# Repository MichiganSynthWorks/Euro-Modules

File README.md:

# Euro-Modules
Euro Module Projects

*[2HP2CV] 2HP Eurorack adaptapation of CVpal, orginal design be Emille Gillet / Mutable Instruments

License
=======

Code (AVR projects): GPL3.0.

Code (STM32F projects): MIT license.

Hardware: cc-by-sa-3.0

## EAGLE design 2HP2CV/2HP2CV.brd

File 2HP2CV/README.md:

# 2HP2CV USB to CV adapter

Based on [MI CV Pal](https://github.com/pichenettes/cvpal) by émilie gillet

License
=======

Code (AVR projects): GPL3.0.

Code (STM32F projects): MIT license.

Hardware: cc-by-sa-3.0

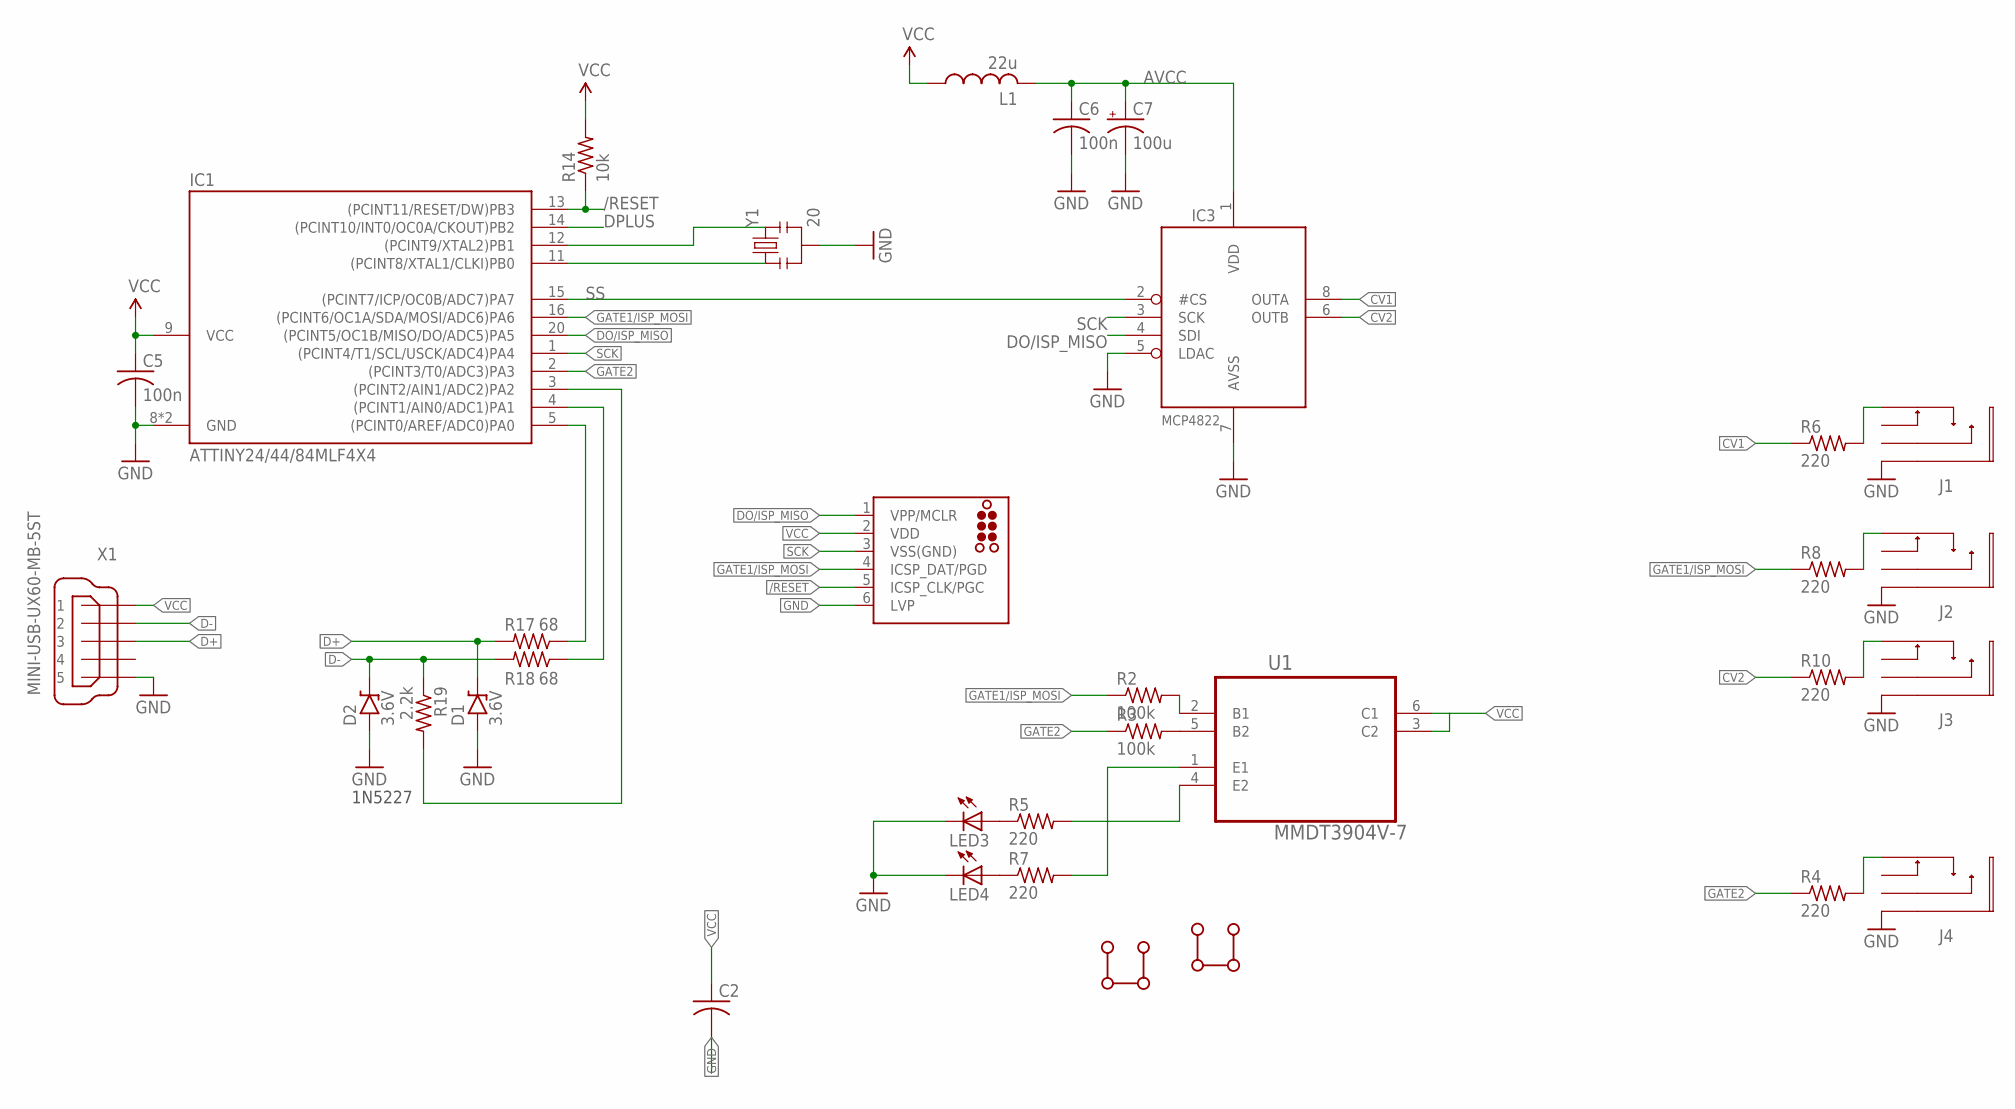
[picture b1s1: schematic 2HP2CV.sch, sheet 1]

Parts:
C2: C-USC0805K; C0805K
C5, C6: 100n; C0402
C7: 100u; A/3216-18R
D1, D2: 3.6V; SOD323-R
IC1: ATTINY24/44/84MLF4X4; MLF20-4X4
IC3: MCP4822SO08; SO08
J1, J2, J3, J4: PJ327E; PJ327
J5: TC2030-MCP-NL
L1: 22u; L2012C
LED3, LED4: LED3MM
R2, R3: 100k; R0402
R4, R5, R6, R7, R8, R10: 220; R0402
R14: 10k; R0402
R17, R18: 68; R0402
R19: 2.2k; R0402
U1: MMDT3904V-7; SOT50P170X60-6N
U$5, U$6: PCB-69M3
X1: MINI-USB-UX60-MB-5ST; UX60-MB-5ST
Y1: 20; RESONATOR-SMD

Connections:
/RESET: IC1.13 ((PCINT11/RESET/DW)PB3), J5.5 (ICSP_CLK/PGC), R14.1
AVCC: C6.1, C7.+, IC3.1 (VDD), L1.2
CV1: IC3.8 (OUTA), R6.1
CV2: IC3.6 (OUTB), R10.1
D+: D1.C, R17.2, X1.3
D-: D2.C, R18.2, R19.1, X1.2
DMINUS: IC1.4 ((PCINT1/AIN0/ADC1)PA1), R18.1
DO/ISP_MISO: IC1.20 ((PCINT5/OC1B/MISO/DO/ADC5)PA5), IC3.4 (SDI), J5.1 (VPP/MCLR)
DPLUS: IC1.5 ((PCINT0/AREF/ADC0)PA0), IC1.14 ((PCINT10/INT0/OC0A/CKOUT)PB2), R17.1
GATE1/ISP_MOSI: IC1.16 ((PCINT6/OC1A/SDA/MOSI/ADC6)PA6), J5.4 (ICSP_DAT/PGD), R2.1, R8.1
GATE2: IC1.2 ((PCINT3/T0/ADC3)PA3), R3.1, R4.1
GND: C2.2, C5.2, C6.2, C7.-, D1.A, D2.A, IC1.8 (GND), IC1.TH (GND), IC3.5 (LDAC), IC3.7 (AVSS), J1.P$1, J2.P$1, J3.P$1, J4.P$1, J5.6 (LVP), LED3.K (C), LED4.K (C), X1.5, Y1.2
unnamed: R3.2, U1.5 (B2)
unnamed: R2.2, U1.2 (B1)
unnamed: J4.P$2, R4.2
unnamed: J3.P$2, R10.2
unnamed: R5.2, U1.4 (E2)
unnamed: R7.2, U1.1 (E1)
unnamed: LED3.A, R5.1
unnamed: J1.P$2, R6.2
unnamed: LED4.A, R7.1
unnamed: J2.P$2, R8.2
unnamed: IC1.12 ((PCINT9/XTAL2)PB1), Y1.3
unnamed: IC1.11 ((PCINT8/XTAL1/CLKI)PB0), Y1.1
unnamed: IC1.3 ((PCINT2/AIN1/ADC2)PA2), R19.2
SCK: IC1.1 ((PCINT4/T1/SCL/USCK/ADC4)PA4), IC3.3 (SCK), J5.3 (VSS(GND))
SS: IC1.15 ((PCINT7/ICP/OC0B/ADC7)PA7), IC3.2 (#CS)
VCC: C2.1, C5.1, IC1.9 (VCC), J5.2 (VDD), L1.1, R14.2, U1.3 (C2), U1.6 (C1), X1.1

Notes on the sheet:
1N5227

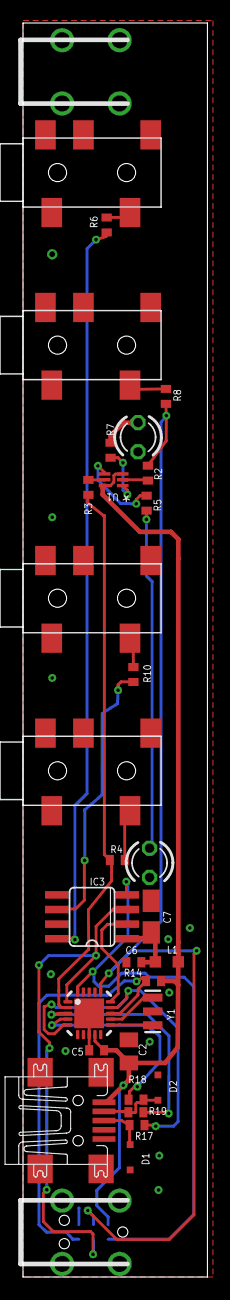
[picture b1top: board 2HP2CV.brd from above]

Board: 2 copper layers, 16.0 x 109.0 mm, 33 parts (1 on the bottom side), 28 nets.

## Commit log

2020-03-16 2HP2CV stuff
2020-03-16 panel added

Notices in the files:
parts and their libraries:
SparkFun-FreqCtrl: Licensing: Creative Commons ShareAlike 4.0 International - https://creativecommons.org/licenses/by-sa/4.0
tag-connect: ©2009 ROFA.cz - modified and updated by Robert Darlington ‹rdarlington@gmail.com›
